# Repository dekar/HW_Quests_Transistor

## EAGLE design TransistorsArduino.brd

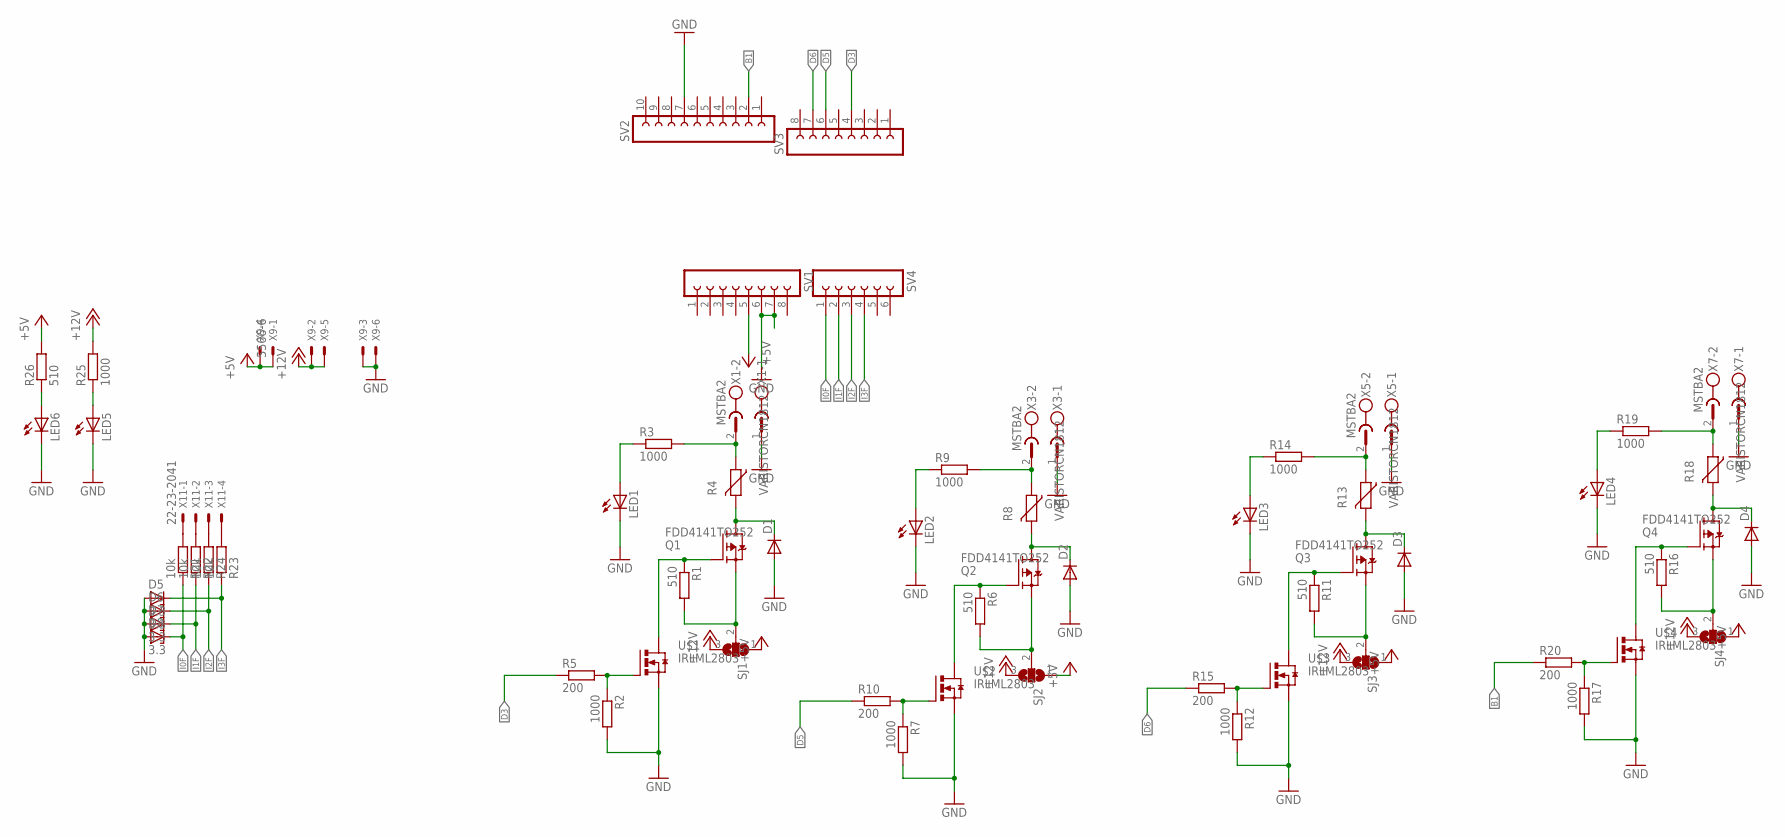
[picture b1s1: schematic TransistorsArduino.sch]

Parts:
D1, D2, D3, D4: DIODE-SMB; SMB
D5, D6, D7, D8: 3.3; SOD80C
LED1, LED2, LED3, LED4, LED5, LED6: LEDCHIPLED_1206; CHIPLED_1206
Q1, Q2, Q3, Q4: FDD4141TO252; TO252
R1, R6, R11, R16, R26: 510; M0805
R2, R3, R7, R9, R12, R14, R17, R19, R25: 1000; M0805
R4, R8, R13, R18: VARISTORCN1812; CT/CN1812
R5, R10, R15, R20: 200; M0805
R21, R22, R23, R24: 10k; M0805
SJ1, SJ2, SJ3, SJ4: SJ2W; SJ_2
SV1, SV3: FE08-1; FE08
SV2: FE10-1; FE10
SV4: FE06-1; FE06
U$1, U$2, U$3, U$4: IRLML2803; SUPER-SOT3
X1, X3, X5, X7: MSTBA2
X9: 5566-6
X11: 22-23-2041; MPN 22-23-2041

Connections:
+5V: R26.2, SJ1.1, SJ2.1, SJ3.1, SJ4.1, SV1.5, X9.1, X9.4
+12V: R25.2, SJ1.3, SJ2.3, SJ3.3, SJ4.3, X9.2, X9.5
B1: R20.1, SV2.2
D3: R5.1, SV3.4
D5: R10.1, SV3.6
D6: R15.1, SV3.7
GND: D1.A, D2.A, D3.A, D4.A, D5.A, D6.A, D7.A, D8.A, LED1.C, LED2.C, LED3.C, LED4.C, LED5.C, LED6.C, R2.2, R7.2, R12.2, R17.2, SV1.6, SV1.7, SV2.7, U$1.2 (S), U$2.2 (S), U$3.2 (S), U$4.2 (S), X1.1, X3.1, X5.1, X7.1, X9.3, X9.6
I0F: D8.C, R21.1, SV4.1
I1F: D7.C, R22.1, SV4.2
I2F: D6.C, R24.1, SV4.3
I3F: D5.C, R23.1, SV4.4
unnamed: Q1.2 (S), R1.2, SJ1.2
unnamed: Q1.1 (G), R1.1, U$1.3 (D)
unnamed: R2.1, R5.2, U$1.1 (G)
unnamed: LED1.A, R3.1
unnamed: Q2.2 (S), R6.2, SJ2.2
unnamed: Q2.1 (G), R6.1, U$2.3 (D)
unnamed: R7.1, R10.2, U$2.1 (G)
unnamed: LED2.A, R9.1
unnamed: Q3.2 (S), R11.2, SJ3.2
unnamed: Q3.1 (G), R11.1, U$3.3 (D)
unnamed: R12.1, R15.2, U$3.1 (G)
unnamed: R21.2, X11.1
unnamed: R22.2, X11.2
unnamed: LED3.A, R14.1
unnamed: Q4.2 (S), R16.2, SJ4.2
unnamed: Q4.1 (G), R16.1, U$4.3 (D)
unnamed: R17.1, R20.2, U$4.1 (G)
unnamed: R23.2, X11.4
unnamed: R24.2, X11.3
unnamed: LED4.A, R19.1
unnamed: LED6.A, R26.1
unnamed: LED5.A, R25.1
OUT1: R3.2, R4.1, X1.2
OUT2: R8.1, R9.2, X3.2
OUT3: R13.1, R14.2, X5.2
OUT4: R18.1, R19.2, X7.2
TH1: D1.C, Q1.3 (D), R4.2
TH2: D2.C, Q2.3 (D), R8.2
TH3: D3.C, Q3.3 (D), R13.2
TH4: D4.C, Q4.3 (D), R18.2

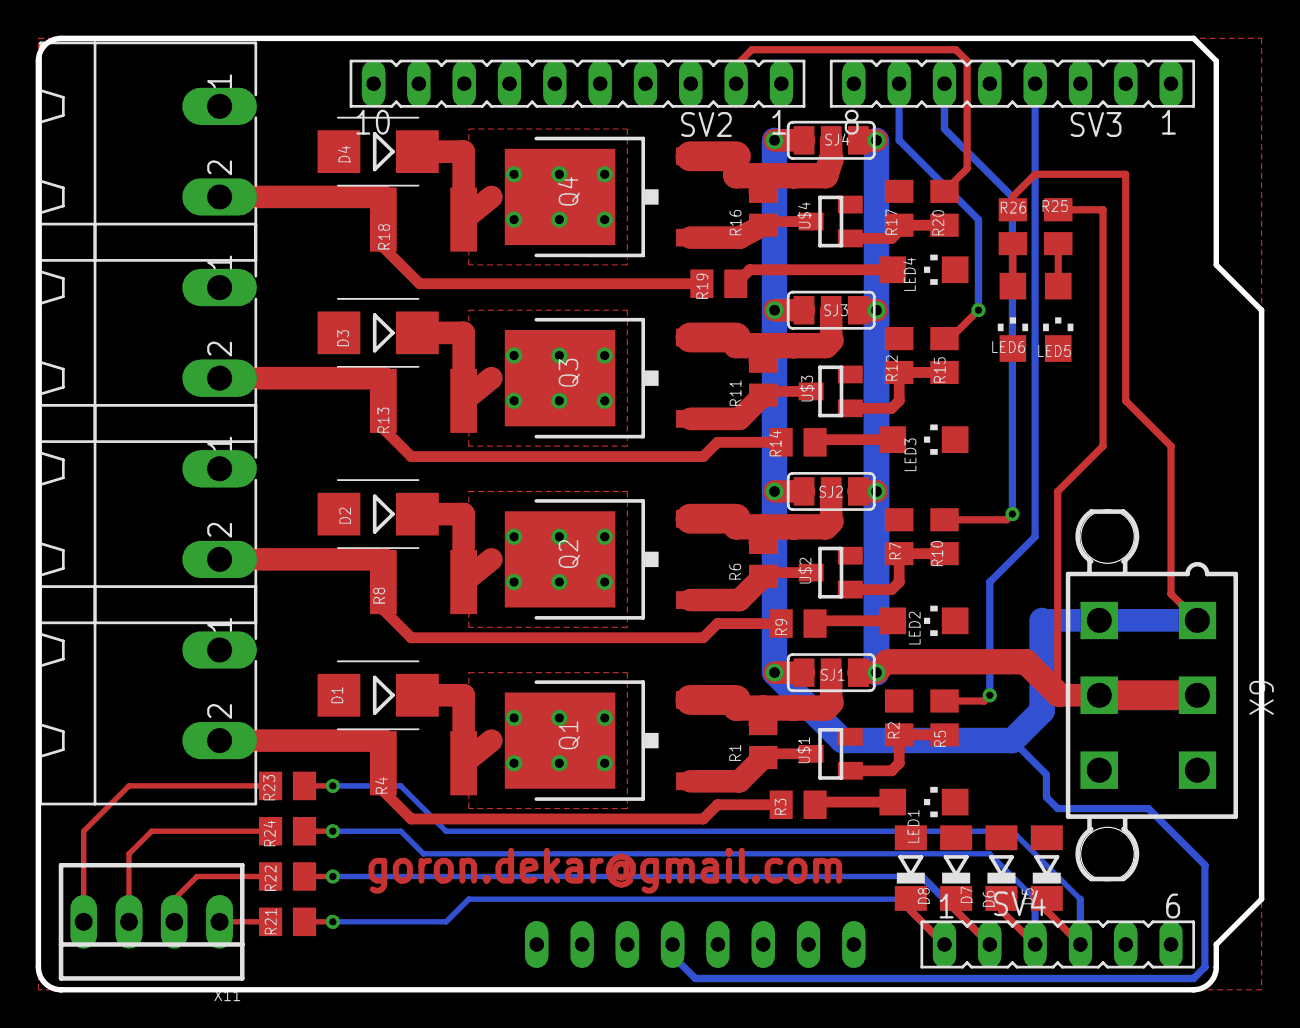
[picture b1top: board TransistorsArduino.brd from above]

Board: 2 copper layers, 68.6 x 53.3 mm, 62 parts (1 on the bottom side), 41 nets.

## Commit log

2014-10-08 New repo. V 1.0
2014-10-08 regenerate gerber files
2014-10-09 220um fix
2014-10-15 Add values + create compile scheme
2014-11-06 Add arduino shield
